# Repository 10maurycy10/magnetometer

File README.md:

# Fluxgate magnetometer datalogger

Data is logged to a microSD/SDHC/SDXC card, which must support SPI mode.
It should be formated as FAT12, FAT16, FAT32 or ExFAT.
If it has an MBR partion table, the first partion will be used.

Most sub 2 TB cards should work as is.

Data is logged to `FLUXGATE.CSV`, in a CSV format.

|First field|Second field format|Notes|
|-|-|-|
|empty string|empty string|Startup banner, includes third field with human readable comment|
|`Vdiv`|Int (mV)|Measured voltage on the Vdd/2 rail of the opamp filter, written on startup.|
|`Vamp`|Int (mV)|Measured amplifier output voltage, written on startup|
|`Vdiv`|Int (mV)|Measure diffence between Vdd/2 and output, written on startup|
|`OSR`|Int|Oversampling ratio used for measurements|
|`Tlog`|Int (ms)|Time between measurements|
|Int|Int|Field measurements, first field is a counter that increments with each one.|

$$ \text{Reading} = \text{Peak-Peak voltage (mV)} \times 10 \times \text{OSR} $$

# Hardware

It should be able to drive most fluxgates, but I got the best result with a [high permiability, square-loop core](https://www.digikey.com/en/products/detail/toshiba-semiconductor-and-storage/MS21X14X4-5W/4701157)
using the classic ring core configuration:
The drive coil was wound around the entire core, and the sense coil was wound on a 3d printed bobin placed over the core:

With the high gain of the amplifier, the earth's magnetic field (50 uT at my place) is enough to saturate the sensor. 
Alternativly, the compensation driver can be enabled to cancel out the field, but the driver can only push current in one direction, so the sensor might have to be flipped for this to work.

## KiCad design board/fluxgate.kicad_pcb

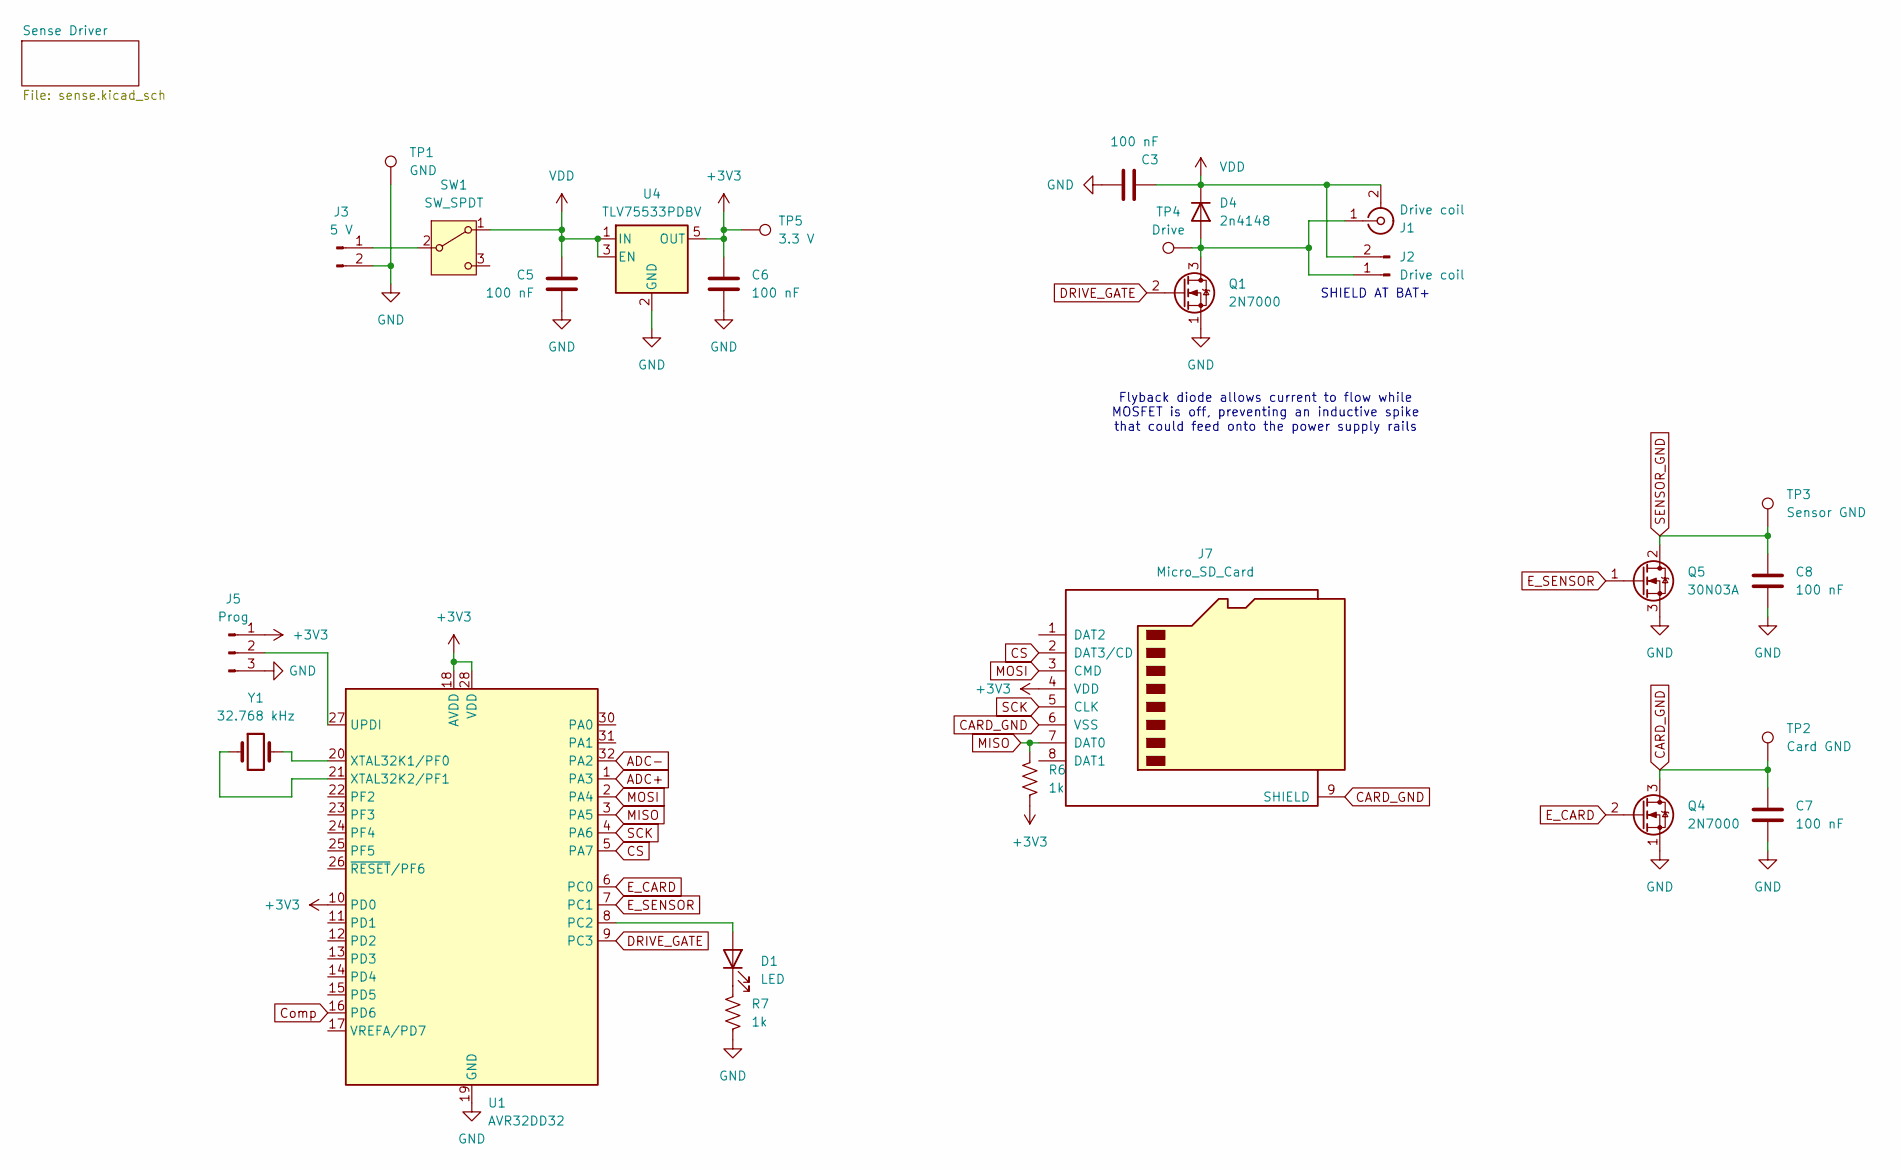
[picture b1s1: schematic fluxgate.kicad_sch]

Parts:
C3, C5, C6, C7, C8: 100 nF; C_Disc_D3.4mm_W2.1mm_P2.50mm
D1: LED; LED_D3.0mm
D4: 2n4148; D_DO-34_SOD68_P7.62mm_Horizontal
J1: Drive coil; SMA_Amphenol_132289_EdgeMount
J2: Drive coil; PinHeader_1x02_P2.54mm_Vertical
J3: 5 V; PinHeader_1x02_P2.54mm_Vertical
J5: Prog; PinHeader_1x03_P2.54mm_Vertical
J7: Micro_SD_Card; microSD_HC_Molex_104031-0811
Q1, Q4: 2N7000; TO-92_Inline
Q5: 30N03A; TO-252-2
R6, R7: 1k; R_Axial_DIN0207_L6.3mm_D2.5mm_P10.16mm_Horizontal
SW1: SW_SPDT; SW_E-Switch_EG1271_SPDT
TP1: GND; TestPoint_Keystone_5015_Micro-Minature
TP2: Card GND; TestPoint_Keystone_5015_Micro-Minature
TP3: Sensor GND; TestPoint_Keystone_5015_Micro-Minature
TP4: Drive; TestPoint_Keystone_5015_Micro-Minature
TP5: 3.3 V; TestPoint_Keystone_5015_Micro-Minature
U1: AVR32DD32; TQFP-32_7x7mm_P0.8mm
U4: TLV75533PDBV; SOT-23-5
Y1: 32.768 kHz; Crystal_HC52-8mm_Vertical

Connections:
+3V3: C6.2, J5.1, J7.4 (VDD), R6.2, TP5.1, U1.10 (PD0), U1.18 (AVDD), U1.28 (VDD), U4.5 (OUT); also elsewhere on the board
ADC+: U1.1 (PA3); also elsewhere on the board
ADC-: U1.32 (PA2); also elsewhere on the board
CARD_GND: C7.1, J7.6 (VSS), J7.9 (SHIELD), Q4.3 (D), TP2.1
CS: J7.2 (DAT3/CD), U1.5 (PA7)
Comp: U1.16 (PD6); also elsewhere on the board
DRIVE_GATE: Q1.2 (G), U1.9 (PC3)
E_CARD: Q4.2 (G), U1.6 (PC0)
E_SENSOR: Q5.1 (G), U1.7 (PC1)
GND: C3.2, C5.1, C6.1, C7.2, C8.2, J3.2, J5.3, Q1.1 (S), Q4.1 (S), Q5.3 (S), R7.2, TP1.1, U1.19 (GND), U1.29 (GND), U4.2 (GND); also elsewhere on the board
MISO: J7.7 (DAT0), R6.1, U1.3 (PA5)
MOSI: J7.3 (CMD), U1.2 (PA4)
unnamed: D1.2 (A), U1.8 (PC2)
unnamed: D1.1 (K), R7.1
unnamed: D4.2 (A), J1.1 (In), J2.1, Q1.3 (D), TP4.1
unnamed: J3.1, SW1.2 (B)
unnamed: J5.2, U1.27 (UPDI)
unnamed: U1.20 (XTAL32K1/PF0), Y1.2
unnamed: U1.21 (XTAL32K2/PF1), Y1.1
SCK: J7.5 (CLK), U1.4 (PA6)
SENSOR_GND: C8.1, Q5.2 (D), TP3.1; also elsewhere on the board
VDD: C3.1, C5.2, D4.1 (K), J1.2 (Ext), J2.2, SW1.1 (A), U4.1 (IN), U4.3 (EN)

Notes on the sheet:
SHIELD AT BAT+
Flyback diode allows current to flow while MOSFET is off, preventing an inductive spike that could feed onto the power supply rails

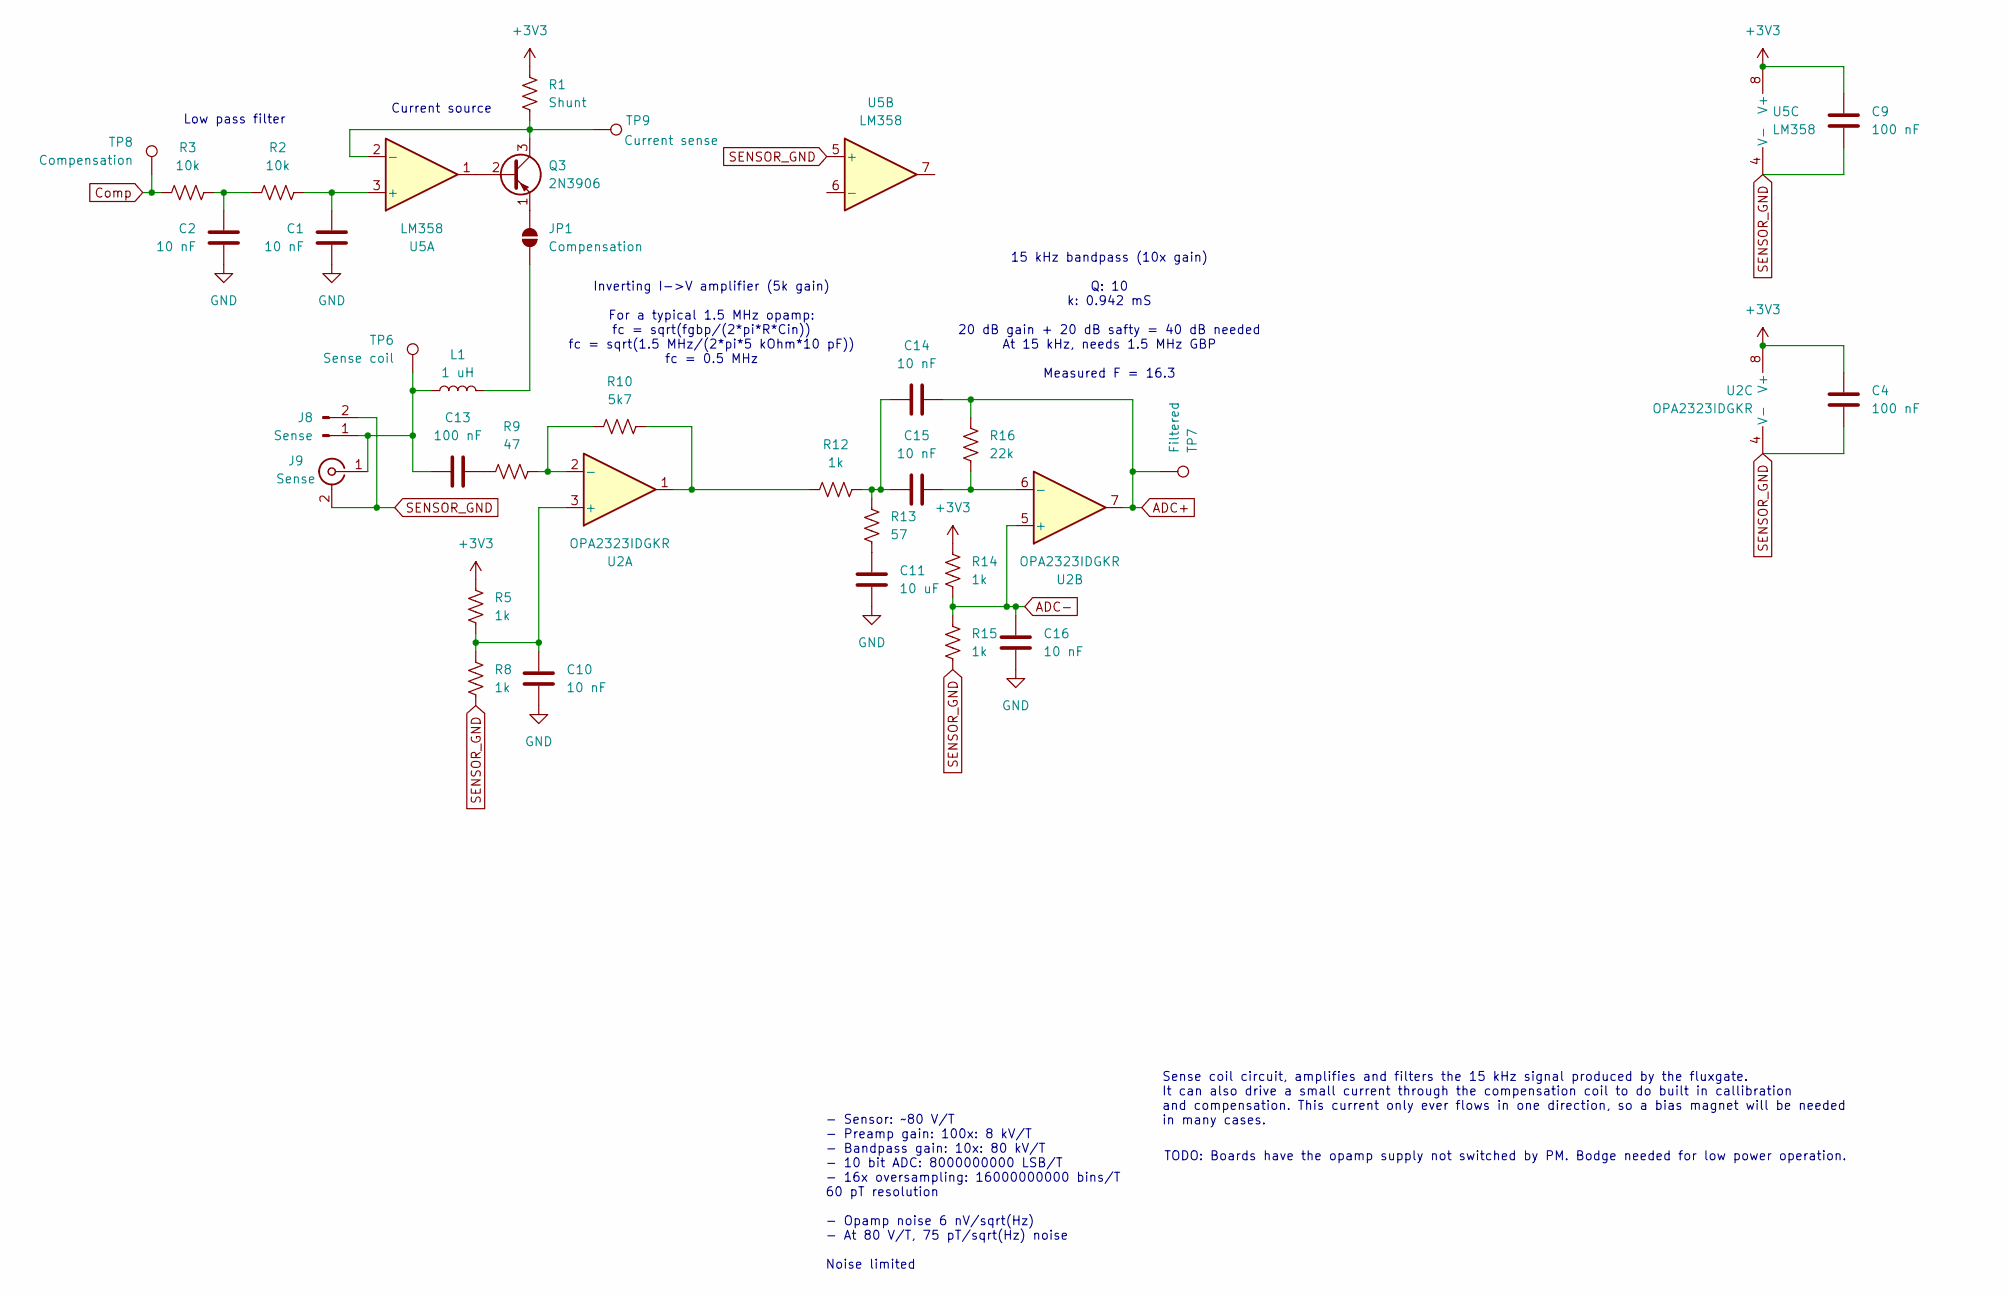
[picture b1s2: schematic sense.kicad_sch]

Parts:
C1, C2, C10, C14, C15, C16: 10 nF; C_Disc_D3.4mm_W2.1mm_P2.50mm
C4, C9, C13: 100 nF; C_Disc_D3.4mm_W2.1mm_P2.50mm
C11: 10 uF; C_Disc_D3.4mm_W2.1mm_P2.50mm
J8: Sense; PinHeader_1x02_P2.54mm_Vertical
J9: Sense; SMA_Amphenol_132289_EdgeMount
JP1: Compensation; SolderJumper-2_P1.3mm_Open_RoundedPad1.0x1.5mm
L1: 1 uH; L_Radial_D7.2mm_P3.00mm_Murata_1700
Q3: 2N3906; TO-92_Inline
R1: Shunt; R_Axial_DIN0207_L6.3mm_D2.5mm_P10.16mm_Horizontal
R2, R3: 10k; R_Axial_DIN0207_L6.3mm_D2.5mm_P10.16mm_Horizontal
R5, R8, R12, R14, R15: 1k; R_Axial_DIN0207_L6.3mm_D2.5mm_P10.16mm_Horizontal
R9: 47; R_Axial_DIN0207_L6.3mm_D2.5mm_P10.16mm_Horizontal
R10: 5k7; R_Axial_DIN0207_L6.3mm_D2.5mm_P10.16mm_Horizontal
R13: 57; R_Axial_DIN0207_L6.3mm_D2.5mm_P10.16mm_Horizontal
R16: 22k; R_Axial_DIN0207_L6.3mm_D2.5mm_P10.16mm_Horizontal
TP6: Sense coil; TestPoint_Keystone_5015_Micro-Minature
TP7: Filtered; TestPoint_Keystone_5015_Micro-Minature
TP8: Compensation; TestPoint_Keystone_5015_Micro-Minature
TP9: Current sense; TestPoint_Keystone_5015_Micro-Minature
U2: OPA2323IDGKR; SOIC-8W_5.3x5.3mm_P1.27mm
U5: LM358; SOIC-8W_5.3x5.3mm_P1.27mm

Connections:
+3V3: C4.2, C9.2, R1.1, R5.2, R14.2, U2.8 (V+), U5.8 (V+); also elsewhere on the board
ADC+: C14.2, R16.2, TP7.1, U2.7; also elsewhere on the board
ADC-: C16.2, R14.1, R15.2, U2.5 (+); also elsewhere on the board
Comp: R3.1, TP8.1; also elsewhere on the board
GND: C1.1, C2.1, C10.1, C11.1, C16.1; also elsewhere on the board
unnamed: C2.2, R2.1, R3.2
unnamed: C11.2, R13.1
unnamed: C13.2, R9.1
unnamed: C14.1, C15.1, R12.2, R13.2
unnamed: C13.1, J8.1, J9.1 (In), L1.1, TP6.1
unnamed: JP1.1 (A), L1.2
unnamed: JP1.2 (B), Q3.1 (E)
unnamed: Q3.2 (B), U5.1
unnamed: Q3.3 (C), R1.2, TP9.1, U5.2 (-)
unnamed: R10.2, R12.1, U2.1
unnamed: C10.2, R5.1, R8.2, U2.3 (+)
unnamed: R9.2, R10.1, U2.2 (-)
unnamed: C15.2, R16.1, U2.6 (-)
unnamed: C1.2, R2.2, U5.3 (+)
SENSOR_GND: C4.1, C9.1, J8.2, J9.2 (Ext), R8.1, R15.1, U2.4 (V-), U5.4 (V-), U5.5 (+); also elsewhere on the board

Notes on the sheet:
- Sensor: ~80 V/T - Preamp gain: 100x: 8 kV/T - Bandpass gain: 10x: 80 kV/T - 10 bit ADC: 8000000000 LSB/T - 16x oversampling: 16000000000 bins/T 60 pT resolution - Opamp noise 6 nV/sqrt(Hz) - At 80 V/T, 75 pT/sqrt(Hz) noise Noise limited
Inverting I->V amplifier (5k gain) For a typical 1.5 MHz opamp: fc = sqrt(fgbp/(2*pi*R*Cin)) fc = sqrt(1.5 MHz/(2*pi*5 kOhm*10 pF)) fc = 0.5 MHz
Low pass filter
Sense coil circuit, amplifies and filters the 15 kHz signal produced by the fluxgate. It can also drive a small current through the compensation coil to do built in callibration and compensation. This current only ever flows in one direction, so a bias magnet will be needed in many cases.
TODO: Boards have the opamp supply not switched by PM. Bodge needed for low power operation.
15 kHz bandpass (10x gain) Q: 10 k: 0.942 mS 20 dB gain + 20 dB safty = 40 dB needed At 15 kHz, needs 1.5 MHz GBP Measured F = 16.3
Current source

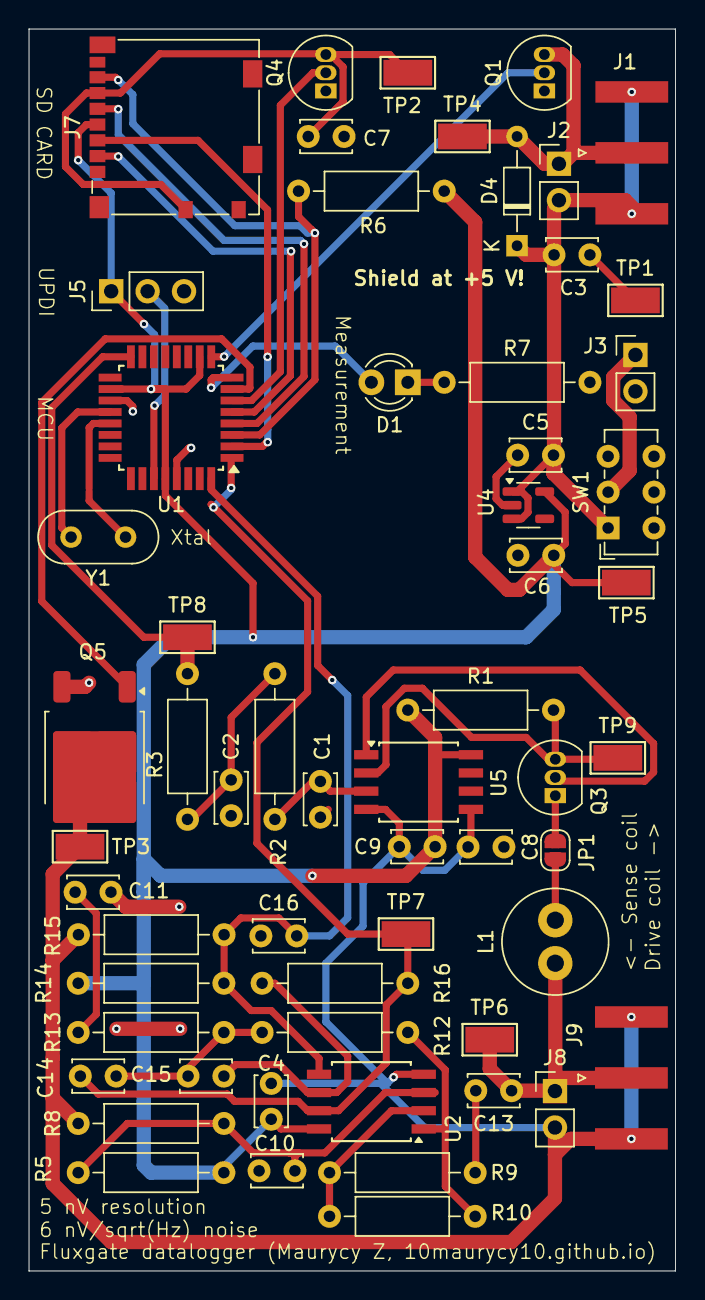
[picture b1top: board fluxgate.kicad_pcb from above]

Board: 2 copper layers, 45.1 x 86.6 mm, 59 parts (0 on the bottom side), 36 nets.

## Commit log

2024-10-30 Board ok
2024-10-31 Fix filesystem, writing files works now
2024-10-31 Comment code
2024-10-31 Commit FAT filesystem library
2024-10-31 Add makefile
2024-10-31 Start working on measurement
2024-10-31 Fixes
2024-11-01 Add untested SD V1 and MMC support
2024-11-03 Perpetual debugging
2024-11-03 it works.
2024-11-03 Keep a constant frequency during measurement
2024-11-03 Select optimal OSR for noise rejection
2024-11-03 Add config file
2024-11-03 Document config file
2024-11-03 Add script to create config file
2024-11-03 Use TCA to controll measurement timing
2024-11-03 Bug fixes
2024-11-04 Disable exfat, saves 10k of flash and 278 bytes ram
2024-11-05 Implement burst mode recording
2024-11-07 Fix PM
2024-11-07 Uncomment code
2024-11-13 Turn off SD card when not in use
